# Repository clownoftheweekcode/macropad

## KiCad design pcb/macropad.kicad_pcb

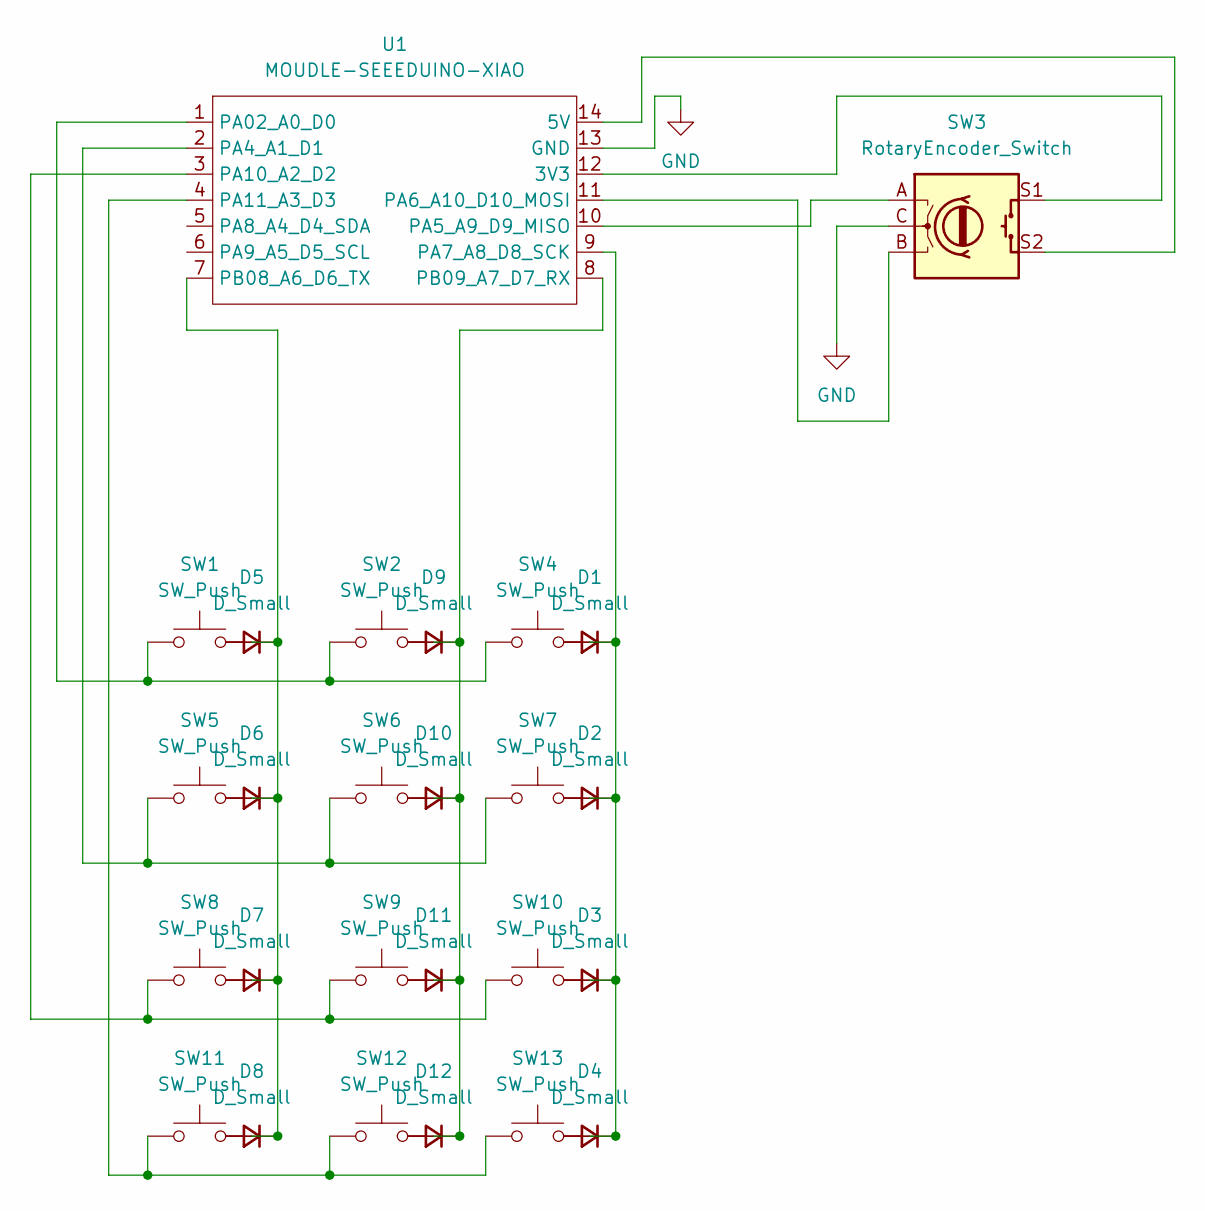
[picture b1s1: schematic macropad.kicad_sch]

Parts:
D1, D2, D3, D4, D5, D6, D7, D8, D9, D10, D11, D12: D_Small; D_DO-35_SOD27_P7.62mm_Horizontal
SW1, SW2, SW4, SW5, SW6, SW7, SW8, SW9, SW10, SW11, SW12, SW13: SW_Push; SW_Cherry_MX_1.00u_PCB
SW3: RotaryEncoder_Switch; RotaryEncoder_Alps_EC11E-Switch_Vertical_H20mm
U1: MOUDLE-SEEEDUINO-XIAO; XIAO-Generic-Hybrid-14P-2.54-21X17.8MM

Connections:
GND: SW3.C, U1.13 (GND)
unnamed: D1.1 (K_1), D2.1 (K_1), D3.1 (K_1), D4.1 (K_1), SW4.2, SW7.2, SW10.2, SW13.2, U1.9 (PA7_A8_D8_SCK)
unnamed: D5.1 (K_1), D6.1 (K_1), D7.1 (K_1), D8.1 (K_1), SW1.2, SW5.2, SW8.2, SW11.2, U1.7 (PB08_A6_D6_TX)
unnamed: D9.1 (K_1), D10.1 (K_1), D11.1 (K_1), D12.1 (K_1), SW2.2, SW6.2, SW9.2, SW12.2, U1.8 (PB09_A7_D7_RX)
unnamed: SW3.S1, U1.12 (3V3)
unnamed: SW3.S2, U1.14 (5V)
unnamed: SW1.1, SW2.1, SW4.1, U1.1 (PA02_A0_D0)
unnamed: SW5.1, SW6.1, SW7.1, U1.2 (PA4_A1_D1)
unnamed: SW3.A, U1.10 (PA5_A9_D9_MISO)
unnamed: SW3.B, U1.11 (PA6_A10_D10_MOSI)
unnamed: SW8.1, SW9.1, SW10.1, U1.3 (PA10_A2_D2)
unnamed: SW11.1, SW12.1, SW13.1, U1.4 (PA11_A3_D3)

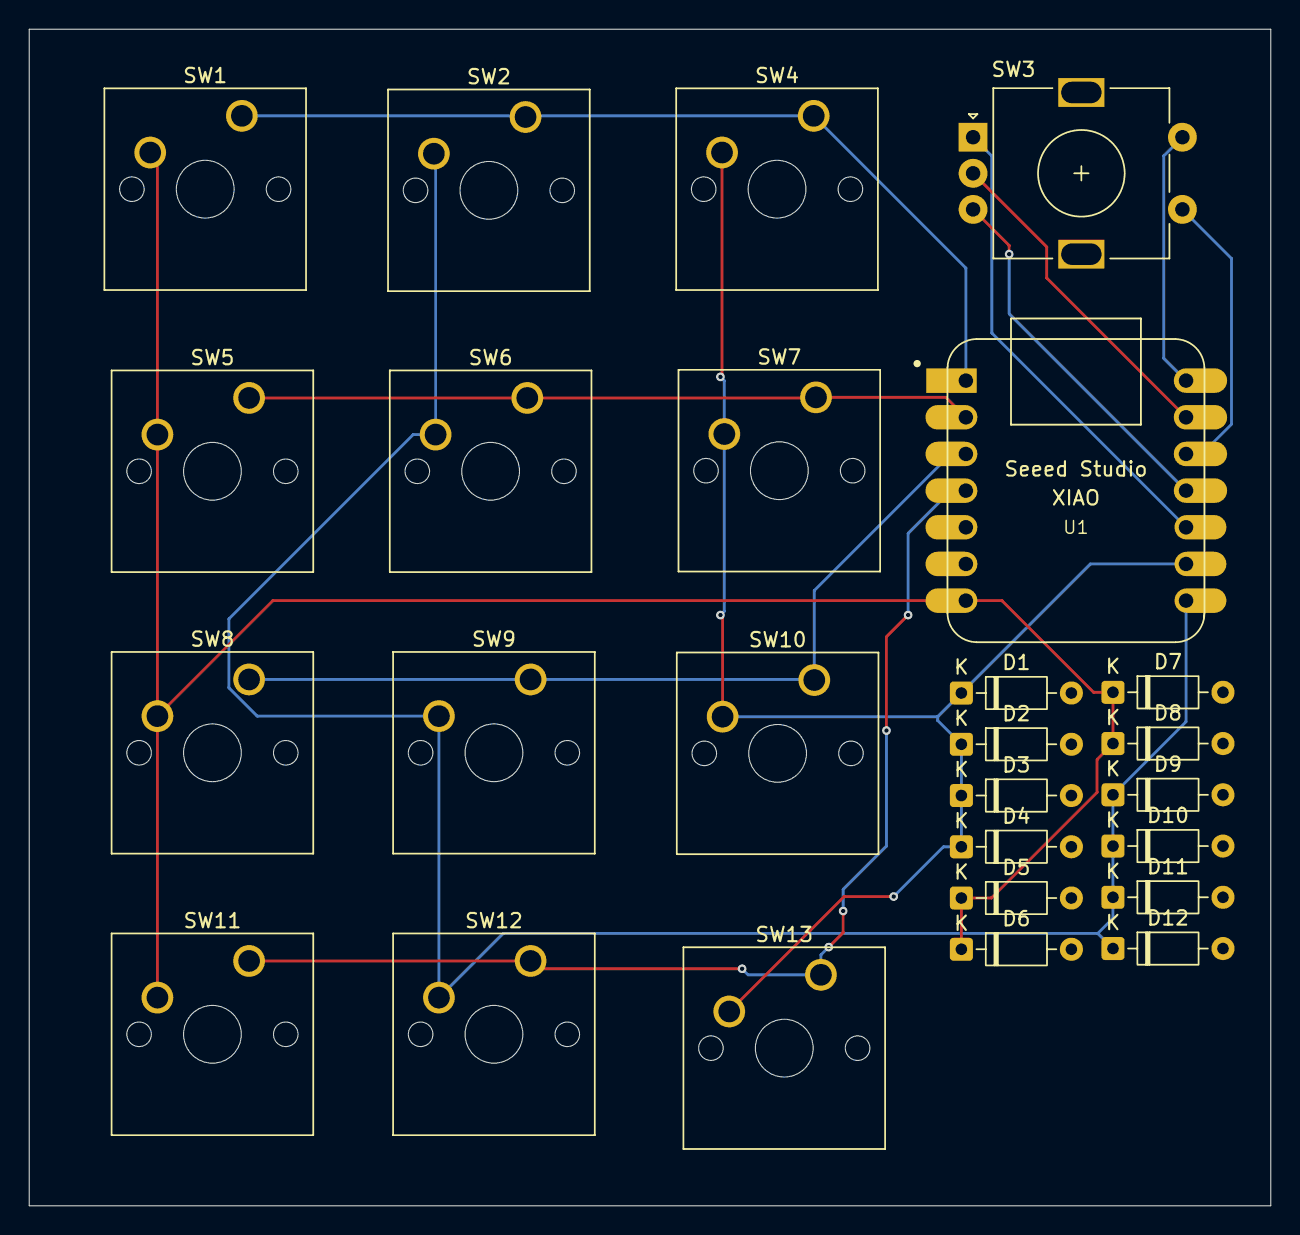
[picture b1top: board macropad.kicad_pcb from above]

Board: 2 copper layers, 86.0 x 81.5 mm, 26 parts (0 on the bottom side), 12 nets.
